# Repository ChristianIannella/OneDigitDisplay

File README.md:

# OneDigitDisplay
I2C interface for 7 segment LCD

<picture><picture>

Con One Digit Display puoi controllare [questi](https://github.com/ChristianIannella/OneDigitDisplay/blob/main/Media/7%20segment%20lcd.png) LCD a 7 segmenti dall'aspetto in po' vintage semplicemente con interfaccia I2C, quindi con solo due fili!

Il modulo lavora a 5V. Tramite la porta ICSP è possibile modificare o aggiornare il firmware. Ecco il mio programmatore [ICSP](https://www.tindie.com/products/30806/)

# I2C COMMAND

Ecco la lista completa dei comandi.

| First byte | Second byte | Symbol|
|         ---|          ---|    ---|
|32          |   0         | Space |
|48          |(0 or 1)     |   0   |
|49          |(0 or 1)     |   1  |
|51          |(0 or 1)     |   2   | 
|50          |(0 or 1)     |   3|
|52          |(0 or 1)     |   4|
|53          |(0 or 1)     |   5|
|54          |(0 or 1)     |   6|
|55          |(0 or 1)     |   7|
|56          |(0 or 1)     |   8|
|57          |(0 or 1)     |   9|
|10          |   0         | Erase|
|46          |   0         |   .|
|45          |(0 or 1)     |    -|
|20          |(0 or 1)     |    ˚|
|65          |(0 or 1)     |   A|
|98          |(0 or 1)     |   b|
|99          |(0 or 1)     |   c|
|67          |(0 or 1)     |    C|
|100         |(0 or 1)     |    d|
|69          |(0 or 1)     |    E|
|70          |(0 or 1)     |     F|
|72          |(0 or 1)     |    H|
|73          |(0 or 1)     |    I|
|76          |(0 or 1)     |    L|
|79          |(0 or 1)     |    O|
|80          |(0 or 1)     |    P|
|83          |(0 or 1)     |    S|
|85          |(0 or 1)     |   U|
|117         |(0 or 1)     |   u|
|27          |(0 or 1)     |  Segment a|
|28          |(0 or 1)     |  Segment b|
|29          |(0 or 1)     |  Segment c|
|30          |(0 or 1)     |  Segment d|
|31          |(0 or 1)     |  Segment e|
|40          |(0 or 1)     |  Segment f|
|33          |(0 or 1)     |  Segment g|
|34          |(1 to 7)     |  DP blink and speed|
|35          |(0 or 1)     |  DP stop|
|36          |(0 to 255)   |  Background color HSV      |                  
|37          |(0 to 255)   |  Backlight brightness|
|38          |(0 to 255)   |  Rainbow effec, default speed 0|
|39          |   0         |  Erase all|

Ogni comando è formato da due Byte, il primo indica la funzione da eseguire e il secondo è un parametro che cambia a seconda della funzione.

Nel di comnadi che stampano caratteri o numeri il parametro puo valere `0`o `1`, `1` attiverà anche il DP `0` no.
I comandi per stampare i caratteri in oltre seguono il codice ASCII.

```
  address = 0
  command[0] = 65;
  command[1] = 1;
  Wire.beginTransmission(address);
  Wire.write(command, sizeof command);
  Wire.endTransmission();
```

L'esempio sopra stamperà la lettera "A" e accenderà il DP del display con indirizzo 0.

Il comando `10` (`erase`) pulisce il display ma lascia attive le altre fuzioni tiopo retroilluminazione ecc. Non necessita di parametri aggiuntivi.

Il comando `34` (`DP blink`) farà lampeggiare il DP con una velocità compresa tra 100 ms e 2s

|Secon Byte|Velocità|
|---|---|
|0|100ms|
|1|200ms|
|2|300ms|
|3|400ms|
|4|500ms|
|5|1000ms|
|6|1500ms|
|7|2000ms|

Esempio:

```
  address = 0
  command[0] = 34;
  command[1] = 4;
  Wire.beginTransmission(address);
  Wire.write(command, sizeof command);
  Wire.endTransmission();
```

Il comando `35` (`DP stop`) blocca il lampeggio del DP e col secondo Byte si puo' decidere se tenerlo acceso o spento.

Il comando `36` serve per cambiare il colore della retroilluminazone tramite il parametro che va da `0` a `255`

Il comando `37` serve per cambiare la luminosità il parametro che va da `0` a `255`

Il comando `38` (`rainbow`) avvia un effetto di colori casuali che cambiano piu' o meno velocemente in base al secondo Byte. Per interrompere l'effetto basta cambiare colore o con il comando `erase_all`.

Il comando `39` fa quello che fa `erase` ma questa volta blocca anche tutte le funzioni attive come `DP blink` o `rainbow`

Il comando `46` mostra il DP, non necessita di parametri.

# I2C ADDRESS
Per indirizzare il display sul retro ci sono 3 dip switch quindi 8 indirizzi possibili, assicurati di dare l'indirizzo desiderato prima di alimentare la scheda.

Nel caso hai bisogno di cambiare indirizzo assicurati di spegnere e riaccendere la schheda dopo averlo cambiato.

# I2C EXAMPLE

```
#include <Wire.h>

int address = 0;
byte command[2];

void setup()
{
  Wire.begin();
  delay(100);

  command[0] = 39; // Erase All Command 
  command[1] = 0;
  Wire.beginTransmission(address);
  Wire.write(command, sizeof command);
  Wire.endTransmission();

  command[0] = 37; // Rainbow
  command[1] = 50;
  Wire.beginTransmission(address);
  Wire.write(command, sizeof command);
  Wire.endTransmission();  
}

void loop(){
}
```

[Esempio completo](https://github.com/ChristianIannella/OneDigitDisplay/tree/main/Example)

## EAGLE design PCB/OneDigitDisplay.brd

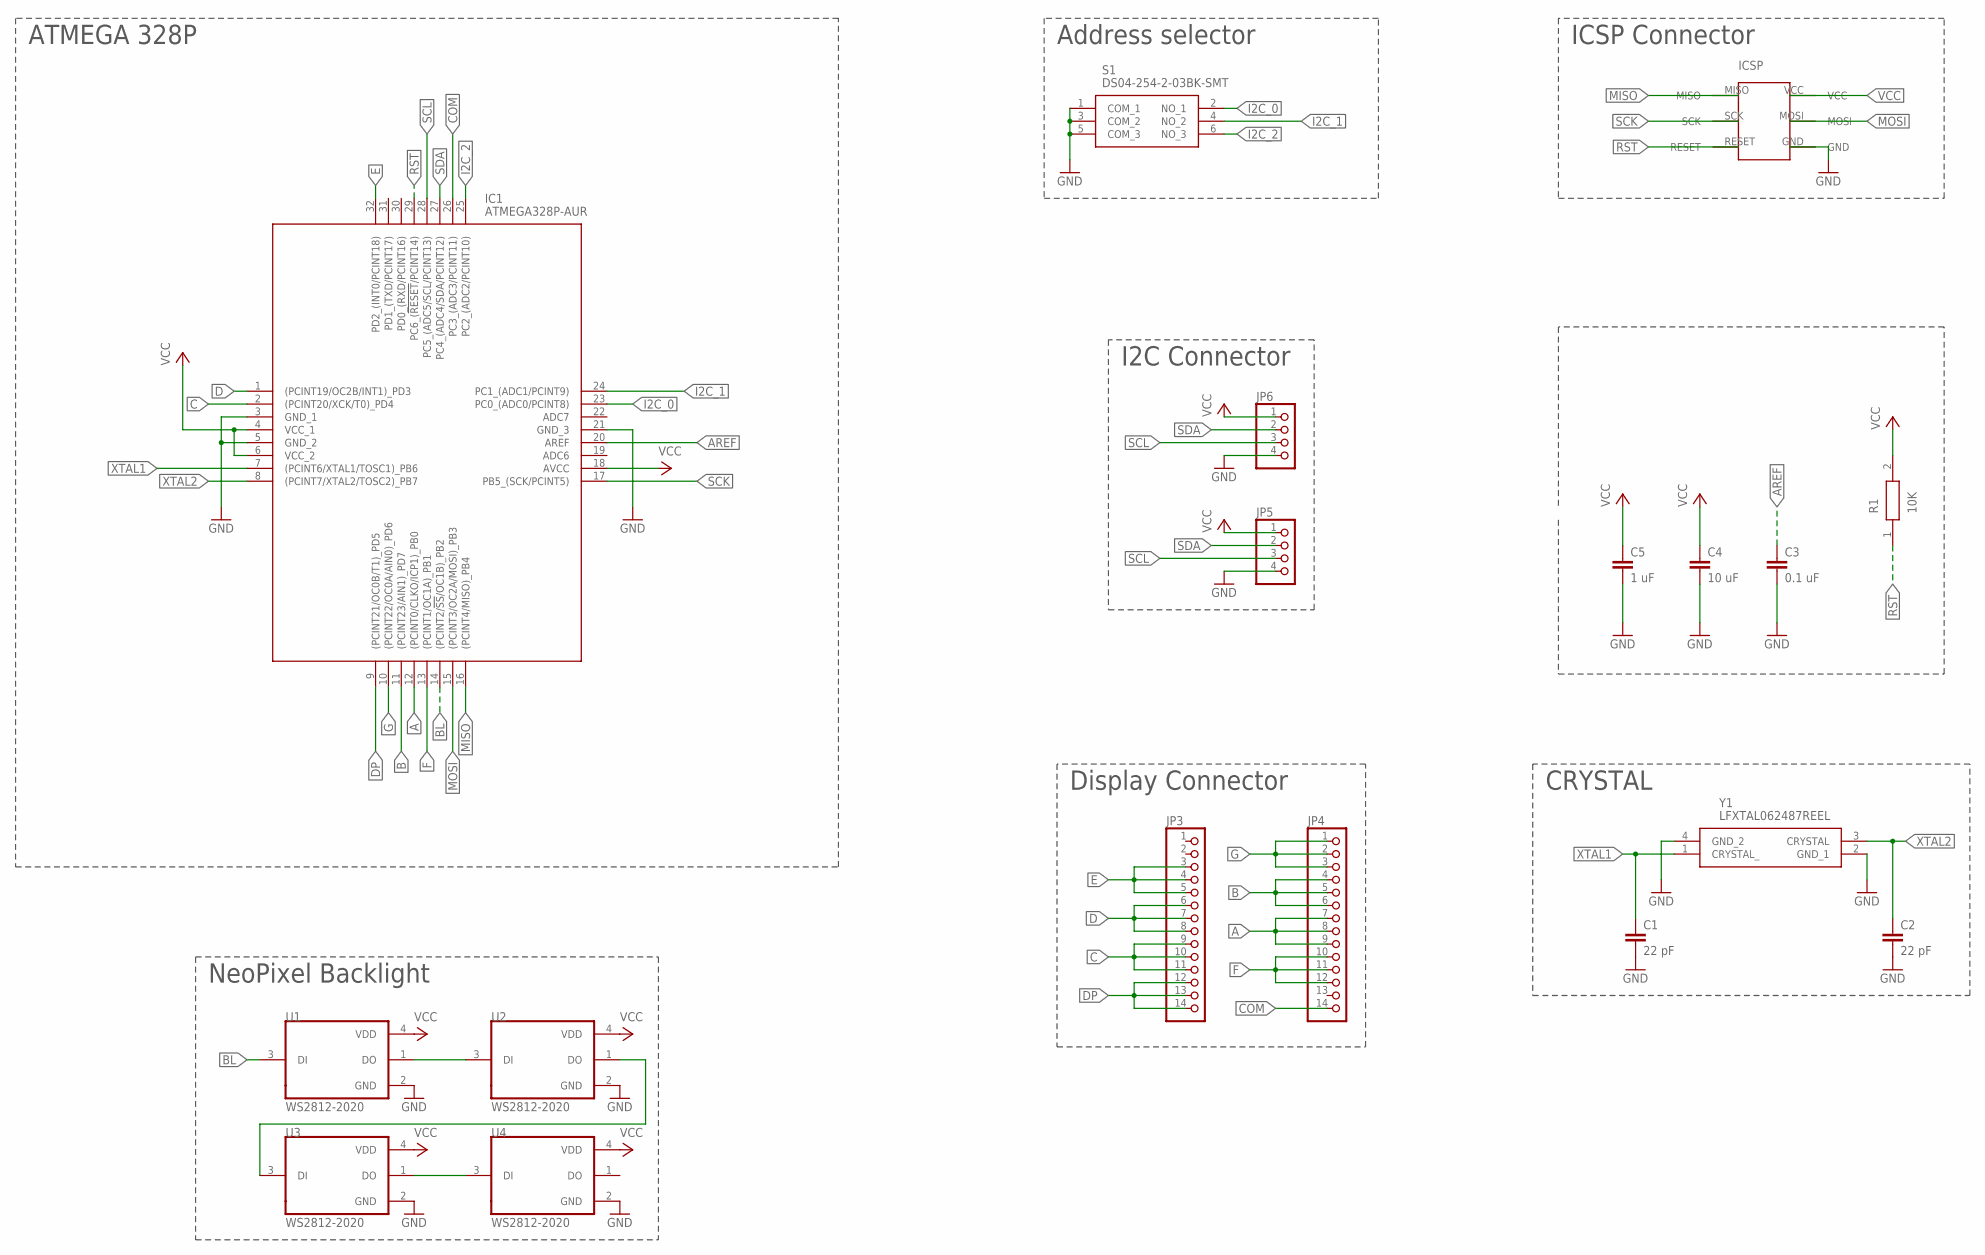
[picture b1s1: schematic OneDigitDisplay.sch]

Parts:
C1, C2: 22 pF; C0603K
C3: 0.1 uF; C0603
C4: 10 uF; C0603
C5: 1 uF; C0603
IC1: ATMEGA328P-AUR; QFP80P900X900X120-32N
JP3, JP4: PINHD-1X14; 1X14
JP5, JP6: PINHD-1X4; 1X04
R1: 10K; RESC1608X55N
S1: DS04-254-2-03BK-SMT; DS04254203BKSMT
U1, U2, U3, U4: WS2812-2020; LED_WS2812-2020
U$1: 6PINICSP
Y1: LFXTAL062487REEL

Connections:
A: IC1.12 ((PCINT0/CLKO/ICP1)_PB0), JP4.7, JP4.8, JP4.9
AREF: C3.1, IC1.20 (AREF)
B: IC1.11 ((PCINT23/AIN1)_PD7), JP4.4, JP4.5, JP4.6
BL: IC1.14 ((PCINT2/!SS!/OC1B)_PB2), U1.3 (DI)
C: IC1.2 ((PCINT20/XCK/T0)_PD4), JP3.9, JP3.10, JP3.11
COM: IC1.26 (PC3_(ADC3/PCINT11)), JP4.14
D: IC1.1 ((PCINT19/OC2B/INT1)_PD3), JP3.6, JP3.7, JP3.8
DP: IC1.9 ((PCINT21/OC0B/T1)_PD5), JP3.12, JP3.13, JP3.14
E: IC1.32 (PD2_(INT0/PCINT18)), JP3.3, JP3.4, JP3.5
F: IC1.13 ((PCINT1/OC1A)_PB1), JP4.10, JP4.11, JP4.12
G: IC1.10 ((PCINT22/OC0A/AIN0)_PD6), JP4.1, JP4.2, JP4.3
GND: C1.2, C2.2, C3.2, C4.2, C5.2, IC1.3 (GND_1), IC1.5 (GND_2), IC1.21 (GND_3), JP5.4, JP6.4, S1.1 (COM_1), S1.3 (COM_2), S1.5 (COM_3), U1.2 (GND), U2.2 (GND), U3.2 (GND), U4.2 (GND), U$1.GND, Y1.2 (GND_1), Y1.4 (GND_2)
I2C_0: IC1.23 (PC0_(ADC0/PCINT8)), S1.2 (NO_1)
I2C_1: IC1.24 (PC1_(ADC1/PCINT9)), S1.4 (NO_2)
I2C_2: IC1.25 (PC2_(ADC2/PCINT10)), S1.6 (NO_3)
MISO: IC1.16 ((PCINT4/MISO)_PB4), U$1.MISO
MOSI: IC1.15 ((PCINT3/OC2A/MOSI)_PB3), U$1.MOSI
unnamed: U1.1 (DO), U2.3 (DI)
unnamed: U2.1 (DO), U3.3 (DI)
unnamed: U3.1 (DO), U4.3 (DI)
RST: IC1.29 (PC6_(!RESET!/PCINT14)), R1.1, U$1.RESET
SCK: IC1.17 (PB5_(SCK/PCINT5)), U$1.SCK
SCL: IC1.28 (PC5_(ADC5/SCL/PCINT13)), JP5.3, JP6.3
SDA: IC1.27 (PC4_(ADC4/SDA/PCINT12)), JP5.2, JP6.2
VCC: C4.1, C5.1, IC1.4 (VCC_1), IC1.6 (VCC_2), IC1.18 (AVCC), JP5.1, JP6.1, R1.2, U1.4 (VDD), U2.4 (VDD), U3.4 (VDD), U4.4 (VDD), U$1.VCC
XTAL1: C1.1, IC1.7 ((PCINT6/XTAL1/TOSC1)_PB6), Y1.1 (CRYSTAL_)
XTAL2: C2.1, IC1.8 ((PCINT7/XTAL2/TOSC2)_PB7), Y1.3 (CRYSTAL)

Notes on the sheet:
CRYSTAL
NeoPixel Backlight
Address selector
ICSP Connector
Display Connector
I2C Connector
ATMEGA 328P

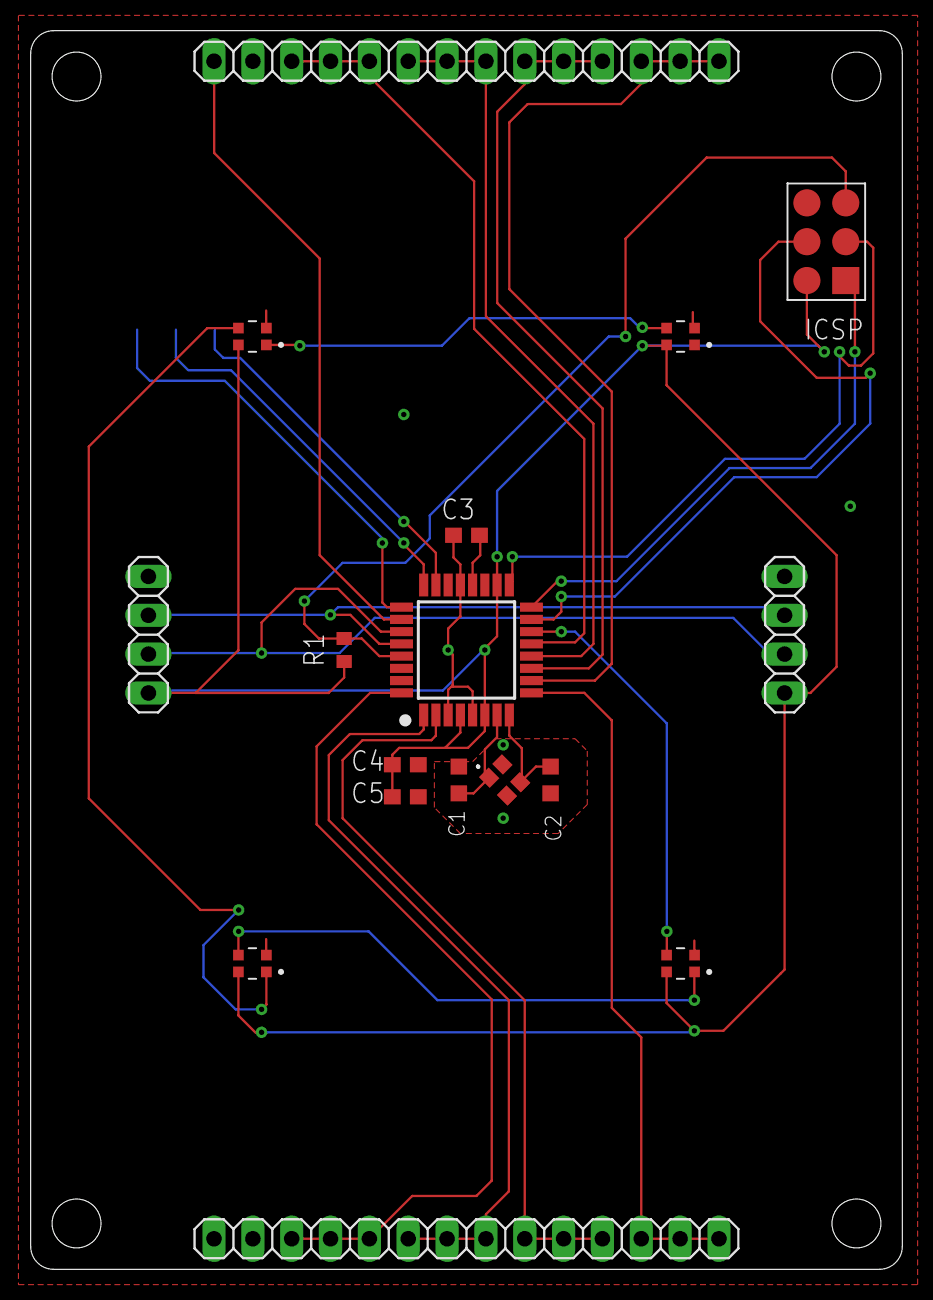
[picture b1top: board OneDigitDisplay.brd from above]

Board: 2 copper layers, 57.0 x 81.0 mm, 18 parts (1 on the bottom side), 27 nets.

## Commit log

2023-10-11 Upload
